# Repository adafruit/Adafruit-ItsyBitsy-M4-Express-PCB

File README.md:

## Adafruit ItsyBitsy M4 Express PCB

<a href="http://www.adafruit.com/products/3800"><br/>
Click here to purchase one from the Adafruit shop</a>

PCB files for the Adafruit ItsyBitsy M4 Express. PCB format is EagleCAD schematic and board layout

For more details, check out the product pages at
* https://www.adafruit.com/products/3800

### Description

What's smaller than a Feather but larger than a Trinket? It's an Adafruit ItsyBitsy M4 Express featuring the Microchip ATSAMD51! Small, powerful, with a ultra fast ATSAMD51 Cortex M4 processor running at 120 MHz - this microcontroller board is perfect when you want something very compact, with a ton of horsepower and a bunch of pins. This Itsy is like a bullet train, with it's 120MHz Cortex M4 with floating point support and 512KB Flash and 192KB RAM. Your code will zig and zag and zoom, and with a bunch of extra peripherals for support, this will for sure be your favorite new chipset.

ItsyBitsy M4 Express is only 1.4" long by 0.7" wide, but has 6 power pins, 23 digital GPIO pins (7 of which can be analog in, 2 x 1 MSPS analog out DACs, and 18 x PWM out). It's the same chip as the Adafruit Metro M4 but really really small. So it's great once you've finished up a prototype on a Metro M4 or (the upcoming) Feather M4, and want to make the project much smaller. It even comes with 2MB of SPI Flash built in, for data logging, file storage, or CircuitPython code.

The most exciting part of the ItsyBitsy M4 is that while you can use it with the Arduino IDE, we are shipping it with CircuitPython on board. When you plug it in, it will show up as a very small disk drive with main.py on it. Edit main.py with your favorite text editor to build your project using Python, the most popular programming language. No installs, IDE or compiler needed, so you can use it on any computer, even ChromeBooks or computers you can't install software on. When you're done, unplug the Itsy' and your code will go with you.

### License

Adafruit invests time and resources providing this open source design, please support Adafruit and open-source hardware by purchasing products from [Adafruit](https://www.adafruit.com)!

Designed by Limor Fried/Ladyada for Adafruit Industries.

Creative Commons Attribution/Share-Alike, all text above must be included in any redistribution. See license.txt for additional details.

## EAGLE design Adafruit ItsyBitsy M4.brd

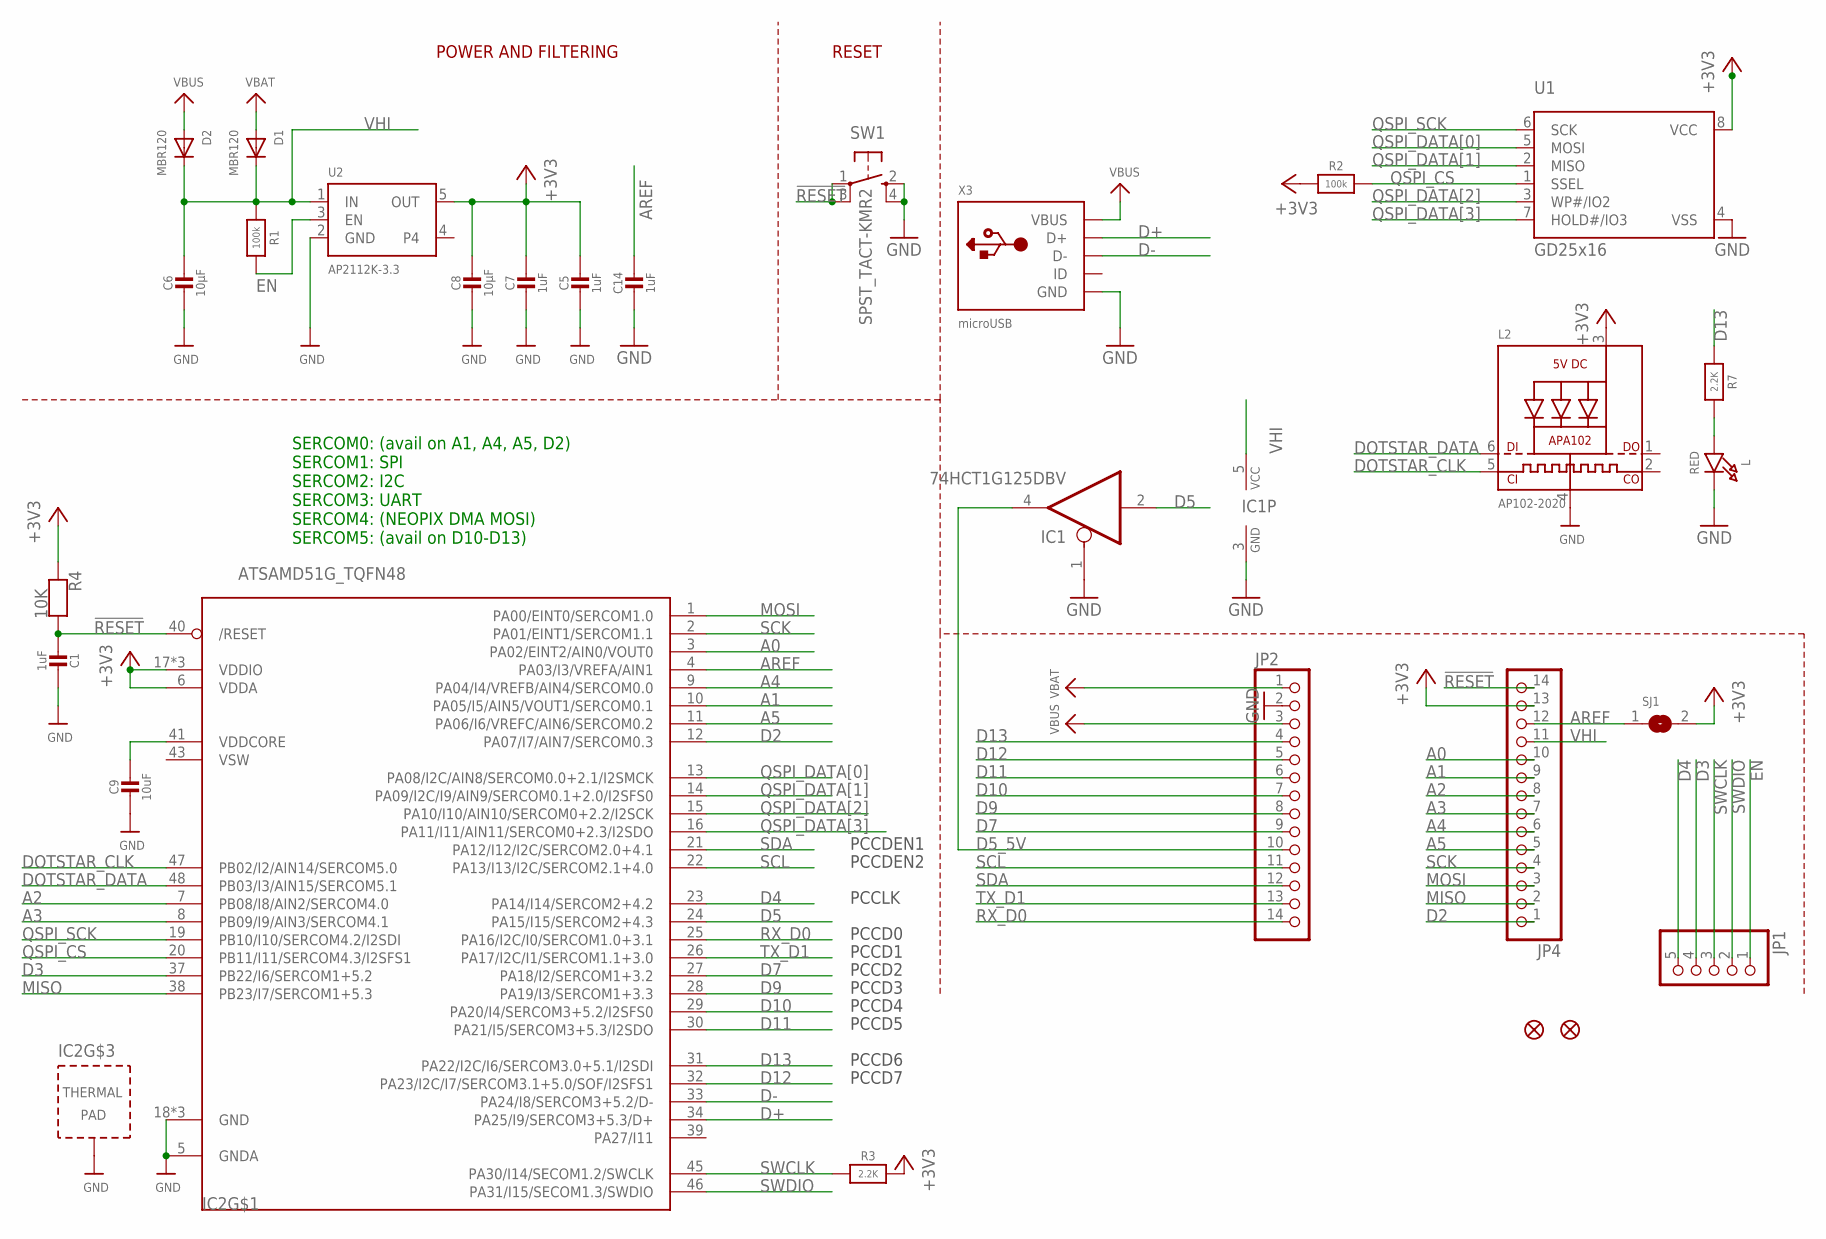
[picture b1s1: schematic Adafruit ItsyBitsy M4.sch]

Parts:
C1: 1uF; _0603MP
C5, C7, C14: 1uF; 0603-NO
C6, C8: 10µF; 0805-NO
C9: 10uF; _0805MP
D1, D2: MBR120; SOD-123FL
IC1: 74HCT1G125DBV; SOT23-5
IC2: ATSAMD51G_TQFN48; TQFN48_7MM
JP1: HEADER-1X570MIL; 1X05_ROUND_70
JP2, JP4: HEADER-1X14; 1X14_ROUND70
L: RED; CHIPLED_0603_NOOUTLINE
L2: AP102-2020; APA102_2020
R1, R2: 100k; 0603-NO
R3: 2.2K; _0603MP
R4: 10K; _0603MP
R7: 2.2K; 0603-NO
SJ1: SOLDERJUMPERCLOSED; SOLDERJUMPER_CLOSEDWIRE
SW1: SPST_TACT-KMR2; KMR2
U1: GD25x16; USON8
U2: AP2112K-3.3; SOT23-5
U$34, U$35: FIDUCIAL_1MM
X3: microUSB; 4UCONN_20329_V2

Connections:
!RESET: C1.2, IC2.40 (/RESET), JP4.14, R4.2, SW1.1, SW1.3 (P1)
+3V3: C5.1, C7.1, C8.1, IC2.6 (VDDA), IC2.17 (VDDIO), IC2.36 (VDDIO), IC2.44 (VDDIO), JP4.13, L2.3 (VDD), R2.1, R3.2, R4.1, SJ1.2, U1.8 (VCC), U2.5 (OUT)
A0: IC2.3 (PA02/EINT2/AIN0/VOUT0), JP4.10
A1: IC2.10 (PA05/I5/AIN5/VOUT1/SERCOM0.1), JP4.9
A2: IC2.7 (PB08/I8/AIN2/SERCOM4.0), JP4.8
A3: IC2.8 (PB09/I9/AIN3/SERCOM4.1), JP4.7
A4: IC2.9 (PA04/I4/VREFB/AIN4/SERCOM0.0), JP4.6
A5: IC2.11 (PA06/I6/VREFC/AIN6/SERCOM0.2), JP4.5
AREF: C14.1, IC2.4 (PA03/I3/VREFA/AIN1), JP4.12, SJ1.1
D2: IC2.12 (PA07/I7/AIN7/SERCOM0.3), JP4.1
D3: IC2.37 (PB22/I6/SERCOM1+5.2), JP1.4
D4: IC2.23 (PA14/I14/SERCOM2+4.2), JP1.5
D5: IC1.2 (I), IC2.24 (PA15/I15/SERCOM2+4.3)
D5_5V: IC1.4 (O), JP2.10
D7: IC2.27 (PA18/I2/SERCOM1+3.2), JP2.9
D9: IC2.28 (PA19/I3/SERCOM1+3.3), JP2.8
D10: IC2.29 (PA20/I4/SERCOM3+5.2/I2SFS0), JP2.7
D11: IC2.30 (PA21/I5/SERCOM3+5.3/I2SDO), JP2.6
D12: IC2.32 (PA23/I2C/I7/SERCOM3.1+5.0/SOF/I2SFS1), JP2.5
D13: IC2.31 (PA22/I2C/I6/SERCOM3.0+5.1/I2SDI), JP2.4, R7.1
D+: IC2.34 (PA25/I9/SERCOM3+5.3/D+), X3.D+
D-: IC2.33 (PA24/I8/SERCOM3+5.2/D-), X3.D-
DOTSTAR_CLK: IC2.47 (PB02/I2/AIN14/SERCOM5.0), L2.5 (CKI)
DOTSTAR_DATA: IC2.48 (PB03/I3/AIN15/SERCOM5.1), L2.6 (DI)
EN: JP1.1, R1.2, U2.3 (EN)
GND: C1.1, C5.2, C6.2, C7.2, C8.2, C9.2, C14.2, IC1.1 (OE), IC1.3 (GND), IC2.5 (GNDA), IC2.18 (GND), IC2.35 (GND), IC2.42 (GND), IC2.THERMAL (TP), JP2.2, L.C, L2.4 (GND), SW1.2 (S), SW1.4 (S1), U1.4 (VSS), U2.2 (GND), X3.BASE@1 (GND), X3.BASE@2 (GND), X3.GND, X3.SPRT@1 (GND), X3.SPRT@2 (GND), X3.SPRT@3 (GND), X3.SPRT@4 (GND)
MISO: IC2.38 (PB23/I7/SERCOM1+5.3), JP4.2
MOSI: IC2.1 (PA00/EINT0/SERCOM1.0), JP4.3
unnamed: L.A, R7.2
QSPI_CS: IC2.20 (PB11/I11/SERCOM4.3/I2SFS1), R2.2, U1.1 (SSEL)
QSPI_DATA[0]: IC2.13 (PA08/I2C/AIN8/SERCOM0.0+2.1/I2SMCK), U1.5 (MOSI)
QSPI_DATA[1]: IC2.14 (PA09/I2C/I9/AIN9/SERCOM0.1+2.0/I2SFS0), U1.2 (MISO)
QSPI_DATA[2]: IC2.15 (PA10/I10/AIN10/SERCOM0+2.2/I2SCK), U1.3 (WP#/IO2)
QSPI_DATA[3]: IC2.16 (PA11/I11/AIN11/SERCOM0+2.3/I2SDO), U1.7 (HOLD#/IO3)
QSPI_SCK: IC2.19 (PB10/I10/SERCOM4.2/I2SDI), U1.6 (SCK)
RX_D0: IC2.25 (PA16/I2C/I0/SERCOM1.0+3.1), JP2.14
SCK: IC2.2 (PA01/EINT1/SERCOM1.1), JP4.4
SCL: IC2.22 (PA13/I13/I2C/SERCOM2.1+4.0), JP2.11
SDA: IC2.21 (PA12/I12/I2C/SERCOM2.0+4.1), JP2.12
SWCLK: IC2.45 (PA30/I14/SECOM1.2/SWCLK), JP1.3, R3.1
SWDIO: IC2.46 (PA31/I15/SECOM1.3/SWDIO), JP1.2
TX_D1: IC2.26 (PA17/I2C/I1/SERCOM1.1+3.0), JP2.13
VBAT: D1.A, JP2.1
VBUS: D2.A, JP2.3, X3.VBUS
VDDCORE: C9.1, IC2.41 (VDDCORE)
VHI: C6.1, D1.C, D2.C, IC1.5 (VCC), JP4.11, R1.1, U2.1 (IN)
VSW: IC2.43 (VSW)

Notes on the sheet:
POWER AND FILTERING
RESET
SERCOM0: (avail on A1, A4, A5, D2) SERCOM1: SPI SERCOM2: I2C SERCOM3: UART SERCOM4: (NEOPIX DMA MOSI) SERCOM5: (avail on D10-D13)
PCCDEN1
PCCDEN2
PCCD0
PCCD1
PCCD2
PCCD3
PCCD4
PCCD5
PCCD6
PCCD7
PCCLK

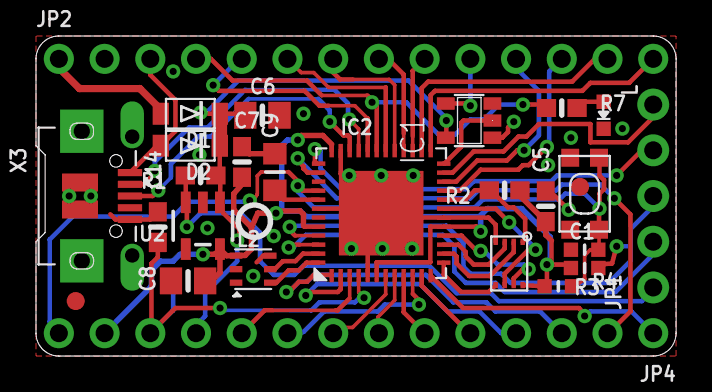
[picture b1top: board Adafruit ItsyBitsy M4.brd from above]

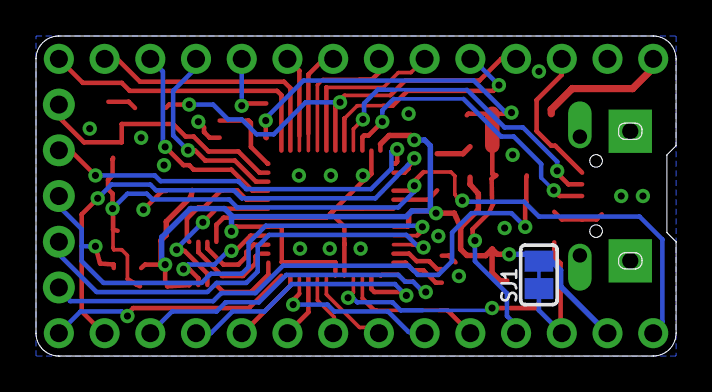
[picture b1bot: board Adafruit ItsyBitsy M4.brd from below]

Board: 2 copper layers, 35.6 x 17.8 mm, 31 parts (2 on the bottom side), 46 nets.

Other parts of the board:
U$4: ITSYM4_TOP
U$5: ITSYM4_BOT
U$6: PCBFEAT-REV-040

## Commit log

2018-06-17 init
2022-06-06 Added PrettyPins

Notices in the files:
parts and their libraries:
microbuilder: This work is placed in the public domain, and may be freely used for commercial and non-commercial work with the following conditions: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
